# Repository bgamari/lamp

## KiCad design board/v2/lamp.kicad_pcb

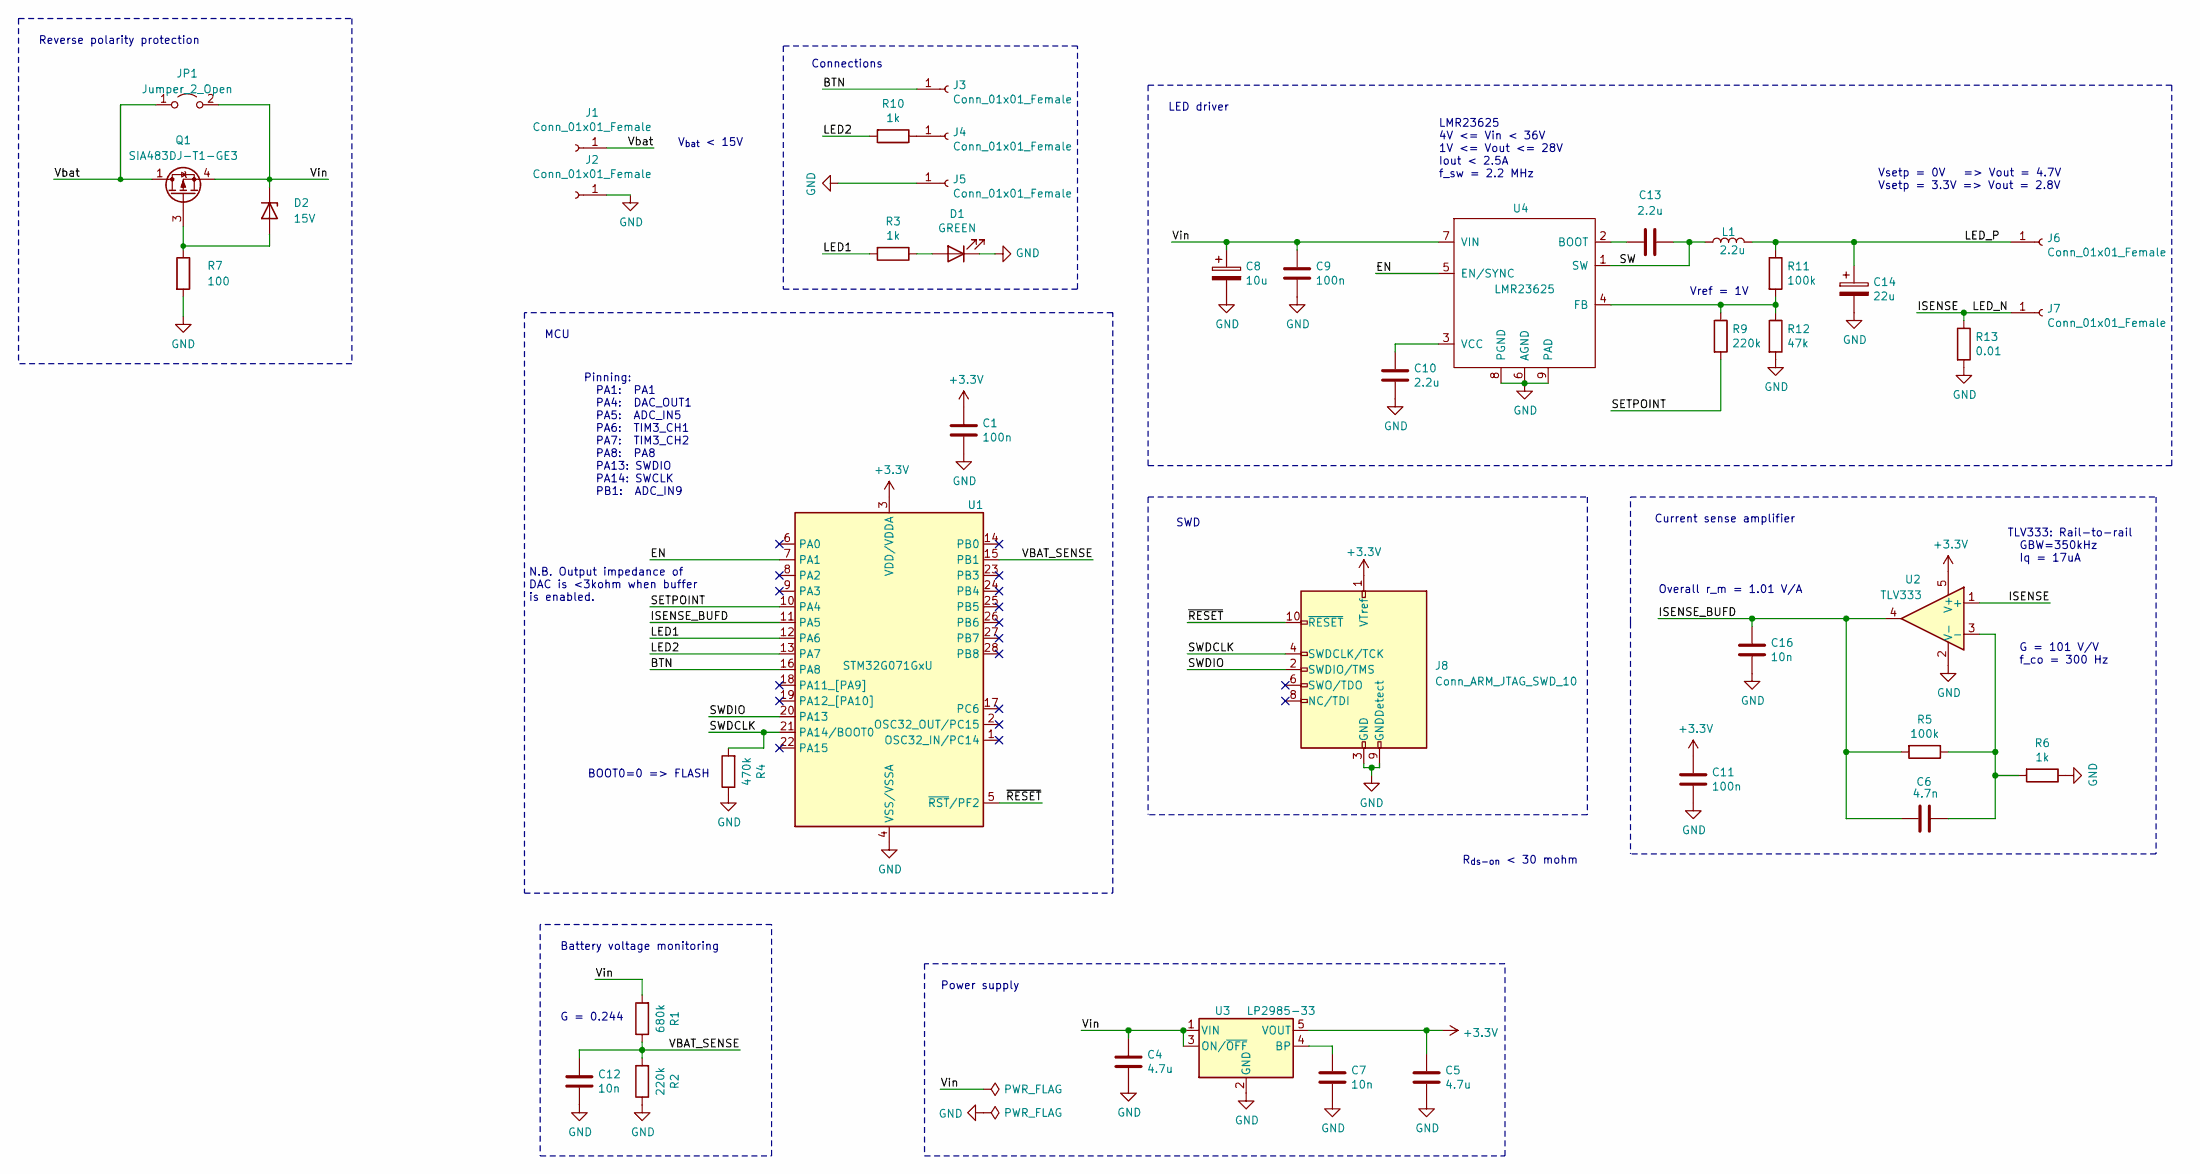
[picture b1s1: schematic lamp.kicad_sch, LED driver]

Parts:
C1, C9, C11: 100n; C_0603_1608Metric
C4: 4.7u; C_0805_2012Metric_Pad1.18x1.45mm_HandSolder
C5: 4.7u; C_0603_1608Metric
C6: 4.7n; C_0603_1608Metric
C7, C12, C16: 10n; C_0603_1608Metric
C8: 10u; CP_EIA-3528-12_Kemet-T; MPN T520B106M016ATE100
C10, C13: 2.2u; C_0603_1608Metric
C14: 22u; CP_EIA-7343-15_Kemet-W; MPN 25TQC22MV
D1: GREEN; LED_0603_1608Metric
D2: 15V; D_SOD-123
J1, J2, J3, J4, J5, J6, J7: Conn_01x01_Female; SolderWirePad_1x01_Drill1mm
J8: Conn_ARM_JTAG_SWD_10; PinHeader_2x05_P1.27mm_Vertical_SMD; MPN 3221-10-0300-00
JP1: Jumper_2_Open; SolderJumper-2_P1.3mm_Open_RoundedPad1.0x1.5mm
L1: 2.2u; L_7.3x7.3_H4.5; MPN DR74-2R2-R
Q1: SIA483DJ-T1-GE3‎; Vishay_PowerPAK_SC70-6L_Single; MPN SIA483DJ-T1-GE3‎
R1: 680k; R_0603_1608Metric
R2, R9: 220k; R_0603_1608Metric
R3, R6, R10: 1k; R_0603_1608Metric
R4: 470k; R_0603_1608Metric
R5, R11: 100k; R_0603_1608Metric
R7: 100; R_0603_1608Metric
R12: 47k; R_0603_1608Metric
R13: 0.01; R_0805_2012Metric; MPN RL1220T-R010-J
U1: STM32G071GxU; QFN-28_4.3x4.3_Pitch0.5mm
U2: TLV333; SOT-353_SC-70-5_Handsoldering
U3: LP2985-33; SOT-23-5; MPN LP2985-33DBVR
U4: LMR23625; SOIC-8-1EP_3.9x4.9mm_P1.27mm_EP2.29x3mm_ThermalVias; MPN TLV62130

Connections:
+3V3: C1.1, C5.1, C11.1, J8.1 (VTref), U1.3 (VDD/VDDA), U2.5 (V+), U3.5 (VOUT)
/BTN: J3.1, U1.16 (PA8)
/EN: U1.7 (PA1), U4.5 (EN/SYNC)
/ISENSE: J7.1, R13.1, U2.1 (+)
/ISENSE_BUFD: C6.2, C16.1, R5.2, U1.11 (PA5), U2.4
/LED1: R3.2, U1.12 (PA6)
/LED2: R10.2, U1.13 (PA7)
/LED_P: C14.1, J6.1, L1.2, R11.1
/SETPOINT: R9.2, U1.10 (PA4)
/SW: C13.2, L1.1, U4.1 (SW)
/SWDCLK: J8.4 (SWDCLK/TCK), R4.2, U1.21 (PA14/BOOT0)
/SWDIO: J8.2 (SWDIO/TMS), U1.20 (PA13)
/VBAT_SENSE: C12.1, R1.1, R2.2, U1.15 (PB1)
/Vbat: J1.1, JP1.1 (A), Q1.1 (D)
/Vin: C4.1, C8.1, C9.1, D2.1 (K), JP1.2 (B), Q1.4 (S), R1.2, U3.1 (VIN), U3.3 (ON/~OFF), U4.7 (VIN)
/~RESET: J8.10 (~RESET), U1.5 (~RST/PF2)
GND: C1.2, C4.2, C5.2, C7.2, C8.2, C9.2, C10.2, C11.2, C12.2, C14.2, C16.2, D1.1 (K), J2.1, J5.1, J8.3 (GND), J8.5 (GND), J8.9 (GNDDetect), R2.1, R4.1, R6.1, R7.2, R12.2, R13.2, U1.4 (VSS/VSSA), U2.2 (V-), U3.2 (GND), U4.6 (AGND), U4.8 (PGND), U4.9 (PAD)
unnamed: C6.1, R5.1, R6.2, U2.3 (-)
unnamed: C7.1, U3.4 (BP)
unnamed: C10.1, U4.3 (VCC)
unnamed: C13.1, U4.2 (BOOT)
unnamed: D1.2 (A), R3.1
unnamed: D2.2 (A), Q1.3 (G), R7.1
unnamed: J4.1, R10.1
unnamed: R9.1, R11.2, R12.1, U4.4 (FB)

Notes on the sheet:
Reverse polarity protection
N.B. Output impedance of DAC is <3kohm when buffer is enabled.
MCU
Battery voltage monitoring
G = 0.244
Pinning: PA1: PA1 PA4: DAC_OUT1 PA5: ADC_IN5 PA6: TIM3_CH1 PA7: TIM3_CH2 PA8: PA8 PA13: SWDIO PA14: SWCLK PB1: ADC_IN9
BOOT0=0 => FLASH
V_{bat} < 15V
Connections
Power supply
LED driver
SWD
LMR23625 4V <= Vin < 36V 1V <= Vout <= 28V Iout < 2.5A f_sw = 2.2 MHz
R_{ds-on} < 30 mohm
Current sense amplifier
Overall r_m = 1.01 V/A
Vref = 1V
Vsetp = 0V => Vout = 4.7V Vsetp = 3.3V => Vout = 2.8V
TLV333: Rail-to-rail GBW=350kHz Iq = 17uA
G = 101 V/V f_co = 300 Hz

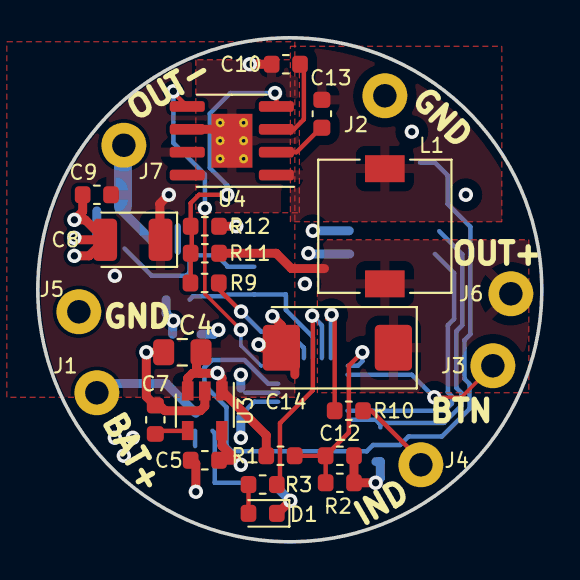
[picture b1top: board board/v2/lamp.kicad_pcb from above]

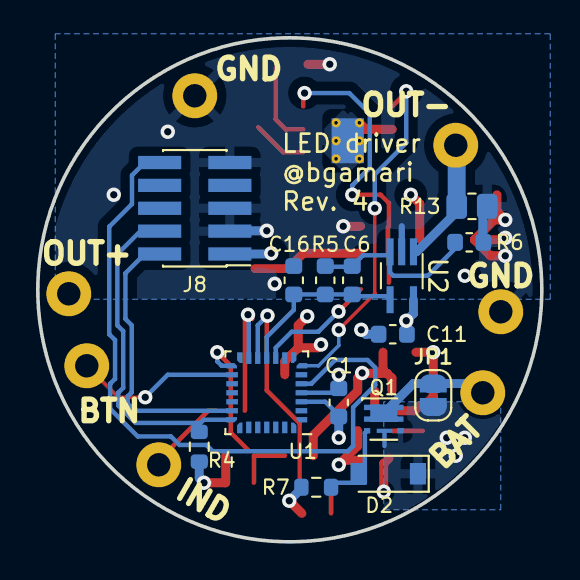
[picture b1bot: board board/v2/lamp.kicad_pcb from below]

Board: 4 copper layers, 28.0 x 28.0 mm, 42 parts (15 on the bottom side), 25 nets.

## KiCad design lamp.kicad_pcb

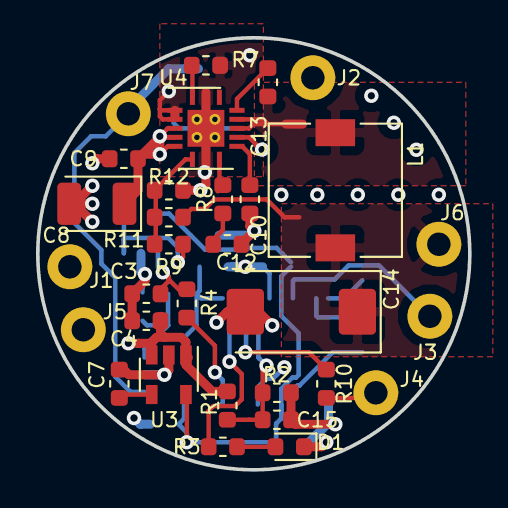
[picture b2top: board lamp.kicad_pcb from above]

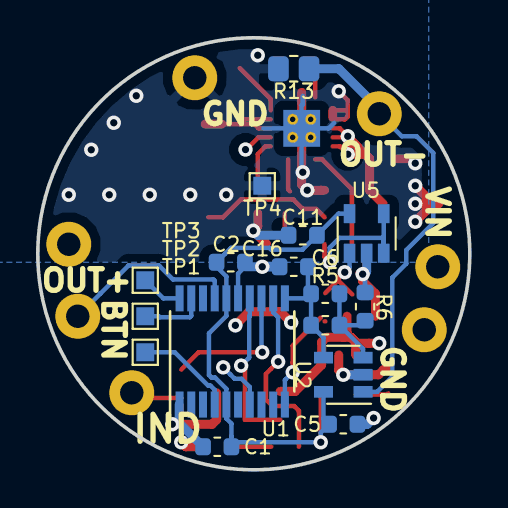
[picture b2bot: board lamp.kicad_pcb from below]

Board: 4 copper layers, 24.0 x 24.0 mm, 47 parts (16 on the bottom side), 28 nets.

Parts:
C1, C2, C4, C5, C6, C7, C9, C11, C13: 100n; C_0603_1608Metric
C3: 1u; C_0603_1608Metric
C8: 10u; CP_EIA-3528-12_Kemet-T
C10, C15, C16: 10n; C_0603_1608Metric
C12: 22n; C_0603_1608Metric
C14: 47u; CP_EIA-7343-15_Kemet-W
D1: LED; LED_0603_1608Metric
J1, J2, J3, J4, J5, J6, J7: Conn_01x01_Female; SolderWirePad_1x01_Drill1mm
L1: 4.7u; L_7.3x7.3_H4.5
R1: 47k; R_0603_1608Metric
R2, R4: 10k; R_0603_1608Metric
R3, R6, R8, R10: 1k; R_0603_1608Metric
R5: 100k; R_0603_1608Metric
R7: 40k; R_0603_1608Metric
R9: 50k; R_0603_1608Metric
R11: 22k; R_0603_1608Metric
R12: 4.7k; R_0603_1608Metric
R13: 0.01; R_0805_2012Metric
TP1, TP2, TP3, TP4: Test_Point; TestPoint_Pad_1.0x1.0mm
U1: STM32F030F4P6; TSSOP-20_4.4x6.5mm_P0.65mm
U2, U5: LMV321; SOT-23-5
U3: MIC5205-3.3; SOT-23-5
U4: TPS54620; Texas_S-PVQFN-N14_ThermalVias

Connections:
+3V3: C1.1, C2.1, C5.1, C11.1, U1.5, U1.16, U2.5, U3.5, U5.5
/BTN: J3.1, U1.17
/EN: U1.7, U4.10
/ISENSE: J7.1, R13.1, U2.1
/LED1: R3.2, U1.12
/LED2: R10.2, U1.13
/LED_P: C14.1, J6.1, L1.2, R11.1
/SETPOINT: C3.1, R4.1, U5.1
/SW: C13.1, L1.1, U4.11, U4.12
/SWCLK: TP3.1, U1.20
/SWDIO: TP2.1, U1.19
/VBAT: C15.1, R1.1, R2.2, U1.14
/VIN: C4.1, C8.1, C9.1, J1.1, R1.2, U3.1, U3.3, U4.4, U4.5, U4.6
GND: C1.2, C2.2, C3.2, C4.2, C5.2, C7.2, C8.2, C9.2, C10.2, C11.2, C12.1, C14.2, C15.2, C16.2, D1.1, J2.1, J5.1, R2.1, R6.1, R7.2, R12.2, R13.2, TP4.1, U1.1, U1.15, U2.2, U3.2, U4.2, U4.3, U4.15, U5.2
unnamed: C6.1, R5.1, R6.2, U2.3
unnamed: C7.1, U3.4
unnamed: C10.1, U4.9
unnamed: C12.2, R8.2
unnamed: C13.2, U4.13
unnamed: C6.2, C16.1, R5.2, U1.11, U2.4
unnamed: D1.2, R3.1
unnamed: J4.1, R10.1
unnamed: R4.2, U1.10
unnamed: R7.1, U4.1
unnamed: R8.1, U4.8
unnamed: R9.2, U5.3, U5.4
unnamed: R9.1, R11.2, R12.1, U4.7
unnamed: TP1.1, U1.4

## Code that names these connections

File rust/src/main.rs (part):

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struct Regulator<'a> {
    adc: embassy_stm32::adc::Adc<'a, embassy_stm32::peripherals::ADC1>,
    dac: embassy_stm32::dac::Dac<'a, embassy_stm32::peripherals::DAC1>,
    isense_pin: embassy_stm32::peripherals::PA5,
    vbat_pin: embassy_stm32::peripherals::PB1,
    out_en: gpio::Output<'a, embassy_stm32::peripherals::PA1>,
}

impl<'a> Regulator<'a> {
    fn read_isense_mA(&mut self) -> u32 {
        let x = self.adc.read(&mut self.isense_pin);
        let isense_mA = self.adc.to_millivolts(x) as u32 * 1000 / 1500;
        isense_mA
    }
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}

static MSGS_CHAN: Forever<mpsc::Channel<kind::CriticalSection, Mode, 1>> = Forever::new();
static BUTTON: Forever<Button<'static, kind::CriticalSection, embassy_stm32::peripherals::PA8>> =
    Forever::new();
static LED1: Forever<Led1<'static>> = Forever::new();

type Led1<'a> = gpio::Output<'a, embassy_stm32::peripherals::PA6>;
type Led2<'a> = gpio::Output<'a, embassy_stm32::peripherals::PA7>;

const VOLTAGE_MODES: [Mode; 13] = [
    Mode::Off,
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async fn main(spawner: Spawner, p: Peripherals) -> ! {
    info!("Hello World!");

    let btn_pin = gpio::Input::new(p.PA8, gpio::Pull::Up);
    let btn_in = exti::ExtiInput::new(btn_pin, p.EXTI8);
    let btn = BUTTON.put(Button::new(btn_in));
    let btn_events = btn.run(&spawner);

    let mut led1: &'static mut Led1 =
        LED1.put(gpio::Output::new(p.PA6, gpio::Level::Low, gpio::Speed::Low));
    let mut led2: Led2 = gpio::Output::new(p.PA7, gpio::Level::Low, gpio::Speed::Low);

    let out_en = gpio::Output::new(p.PA1, gpio::Level::Low, gpio::Speed::Low);

    let adc = embassy_stm32::adc::Adc::new(p.ADC1, &mut Delay);
    let mut dac = embassy_stm32::dac::Dac::new(p.DAC1, p.PA4, gpio::NoPin);
    let isense_pin = p.PA5;
    let vbat_pin = p.PB1;

    blink_ms(&mut led1, Duration::from_millis(100)).await;
    blink_ms(&mut led2, Duration::from_millis(100)).await;
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    let reg = Regulator {
        adc,
        dac,
        isense_pin,
        vbat_pin,
        out_en,
    };
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
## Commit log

2018-06-30 Move to four layers, value selection
2018-06-30 More iteration
2018-06-30 Iterate
2018-06-30 Make LED PWMable
2018-06-30 Make other LED PWMable
2018-06-30 Wibbles
2018-07-02 Use timers that are available on all parts
2018-07-22 First stab at firmware
2018-07-22 Fix semihosting
2018-07-22 firmware: Button support
2018-07-22 Move PWM class out to new source file
2018-07-22 firmware: Enable LTO
2018-07-23 firmware: Things kind of work
2018-07-23 More or less working
2018-07-23 Clean up the code and make it usable
2018-07-23 Try stabilizing feedback
2019-05-18 Add beginnings of Rust firmware
2019-05-19 rust compiles
2019-05-19 Uncommitted changes in C++ firmware
2019-06-01 rust: Use pi_loop
2019-07-03 Fix component values
2019-07-03 Move board design to board/v1
2019-07-03 Fix library paths
2019-07-03 v2 hardware
2019-07-11 Work on Rust firmware
2019-07-12 rust: Feedback roughly works
2019-07-12 hardware: Various fixes
    * Fix component values
    * Replace MIC5202 which wasn't ceramic-stable
2019-07-18 rust firmware generally works
2019-07-18 rust: Add SLEEPDEEP support
2019-07-18 board/v2: Various design changes
    * Switch from MIC5202 to LP2985 due to ceramic stability issues
    with former
    * Use TLV333 for op-amps for reduced power and offset
    * Move current sense amplifier next to sense resistor
2019-07-18 openocd: Make it more robust
2019-07-18 nix: Add ARM gdb
2019-07-18 board/v2: Use two-channel op-amp
2019-07-22 Schematic fixes
2019-07-24 Generalize rust firmware
2019-07-24 Use constant duty cycle mode
2019-08-13 Add missing debounce.rs
2019-08-13 Make debug output optional
2019-08-14 Hardware changes
2019-08-14 Dependency bounds bump
2019-08-14 Reliably register button presses
    The design of stm32f0xx_hal seems antithetical to sensible use of
    interrupts so this was much harder than it should have been. In short,
    it's not possible to clear peripherals status bits in interrupt handlers
    since the library's various abstractions (e.g. `Timer`) expect to do so
    themselves. This essentially precludes use of interrupts since otherwise
    you will loop in the handler.
2019-08-14 Set reasonable default modes
2019-11-21 Red mode
2020-08-14 Uncommitted changes
2020-08-16 Add zlib to LD_LIBRARY_PATH
2020-08-16 Use DigitalPin v2
2020-10-15 Add FreeCAD design
2020-11-15 board/v2: Move to STM32L041F6P7
    This required only a small change in pinning which can be easily bodged
    onto the existing boards.
2021-04-19 hardware: Kicad update
2021-04-19 hardware: Revision 3
    * Increase board size to 28mm diameter
    * Use proper 1.27 mm pin socket for debug
    * Move to STM32L051K MCU
    * Drop thermal cut-out
2021-05-23 Migrate symbol librar
2021-05-26 board: Move to STM32G071
2021-05-29 hardware: Add reverse polarity protection
2021-05-29 Drop fp-info-cache
2021-05-29 hardware: More fiddling
2021-05-29 hardware: More wibbles
2021-05-29 Update symbol library
2021-07-29 board changes
2021-07-29 CAD changes
2021-07-30 board: Drop BOM
2021-07-30 board: Update kicad
2021-07-30 rust: Port to STM32G071
2021-07-31 Port STM32G0 firmware to embassy
2021-08-02 Progress
2021-08-03 More progress
2021-08-03 board: Fix footprint of op-amp
    The pinouts of the SC-70 and SOT-23-5 opamps are incompatible.
2021-08-05 button: await on futures
2021-08-05 rust: Drop unused spin package
2021-08-05 Bump embassy
2021-08-05 rust: Update lock file
2021-08-05 button: Debug output
2021-08-05 rust: Testing
2021-08-30 hardware: Set R7 value
2021-08-30 nix: Add tools for working on embassy
2021-08-30 hw: Changes
2021-08-30 firmware changes
2021-08-31 firmware: Start to implement feedback
2021-08-31 firmware: Feedback works-ish
2021-08-31 firmware: Cleanup warnings
2021-08-31 firmware: Drop old test code
2021-08-31 firmware: Drop dead code
2021-08-31 firmware: Factor out UI
2021-08-31 firmware: minor refactor
2021-08-31 firmware: Enable/disable DAC on output enable toggle
2021-08-31 firmware: Clock down MCU
2021-08-31 firmware: Use blink_ms
2021-08-31 firmware: Reasonably low power
2021-09-28 board: Add pad labels on front
2021-09-28 board: Project file changes
2021-09-28 board: Set resistor value
2021-09-28 firmware: ST-Link openocd configuration
2021-09-28 firmware: Factor out configuration
2021-09-28 firmware: Add battery voltage monitoring
2021-09-28 board: Hardware fixes from assembly
2021-09-28 firmware: Use const
2021-09-28 firmware: Refactor LED handling
2021-09-28 firmware: Fix constants
2021-09-29 Update embassy
2021-10-24 Drop old C++ firmware
2021-10-24 Move rust/ to firmware/
2021-10-24 cad: Update
2021-10-24 Bump embassy submodule
2021-12-29 Add active_state abstraction
2021-12-29 firmware: Bump embassy
2021-12-29 Fix chip name
2021-12-29 firmware: Drop defmt features
2021-12-29 hw: Fix RESET line on JTAG connector
    Previously this was disconnected due to a net name mismatch.
2021-12-29 firmware: Use cargo features
2021-12-29 firmware: Allow DAC to settle after suspend
2021-12-29 active_state: Fix LPMS value
2021-12-29 firmware: Ensure that DAC is disabled until needed
    Fix an embassy bug which broke disable_channel and ensure it is called
    after startup since the channel starts in the enabled state.
2021-12-29 firmware: Ensure PWR is ungated prior to setting LPMS
2021-12-29 firmware: Factor out type synonym
2021-12-29 firmware: Explicitly disable unused peripherals
2021-12-29 firmware: Don't use low-power run
    The ADC is not usable when the low-power regulator is in use (see RM0444
    section 15.3.2). Moreover, it's not necessary now that we use STOP 1
    mode.
2021-12-29 firmware: Disable ADC when not in use
    It's a bit hacky but reduces current from 20uA to 5uA.
2021-12-30 hw: Larger package for LDO input cap
    0603 was too small for a realistic capacitance.
2021-12-30 Bump cortex-m-rt
2021-12-30 firmware: Pause slightly before re-suspending
2021-12-30 firmware: Make suspend non-async
2021-12-30 firmware: Rip out set_adc_enabled
2021-12-30 firmware: Teach button about active_state
2021-12-30 firmware: Increase debounce time
2021-12-30 active_state: Add comment
2022-04-17 firmware: Catch overflow
